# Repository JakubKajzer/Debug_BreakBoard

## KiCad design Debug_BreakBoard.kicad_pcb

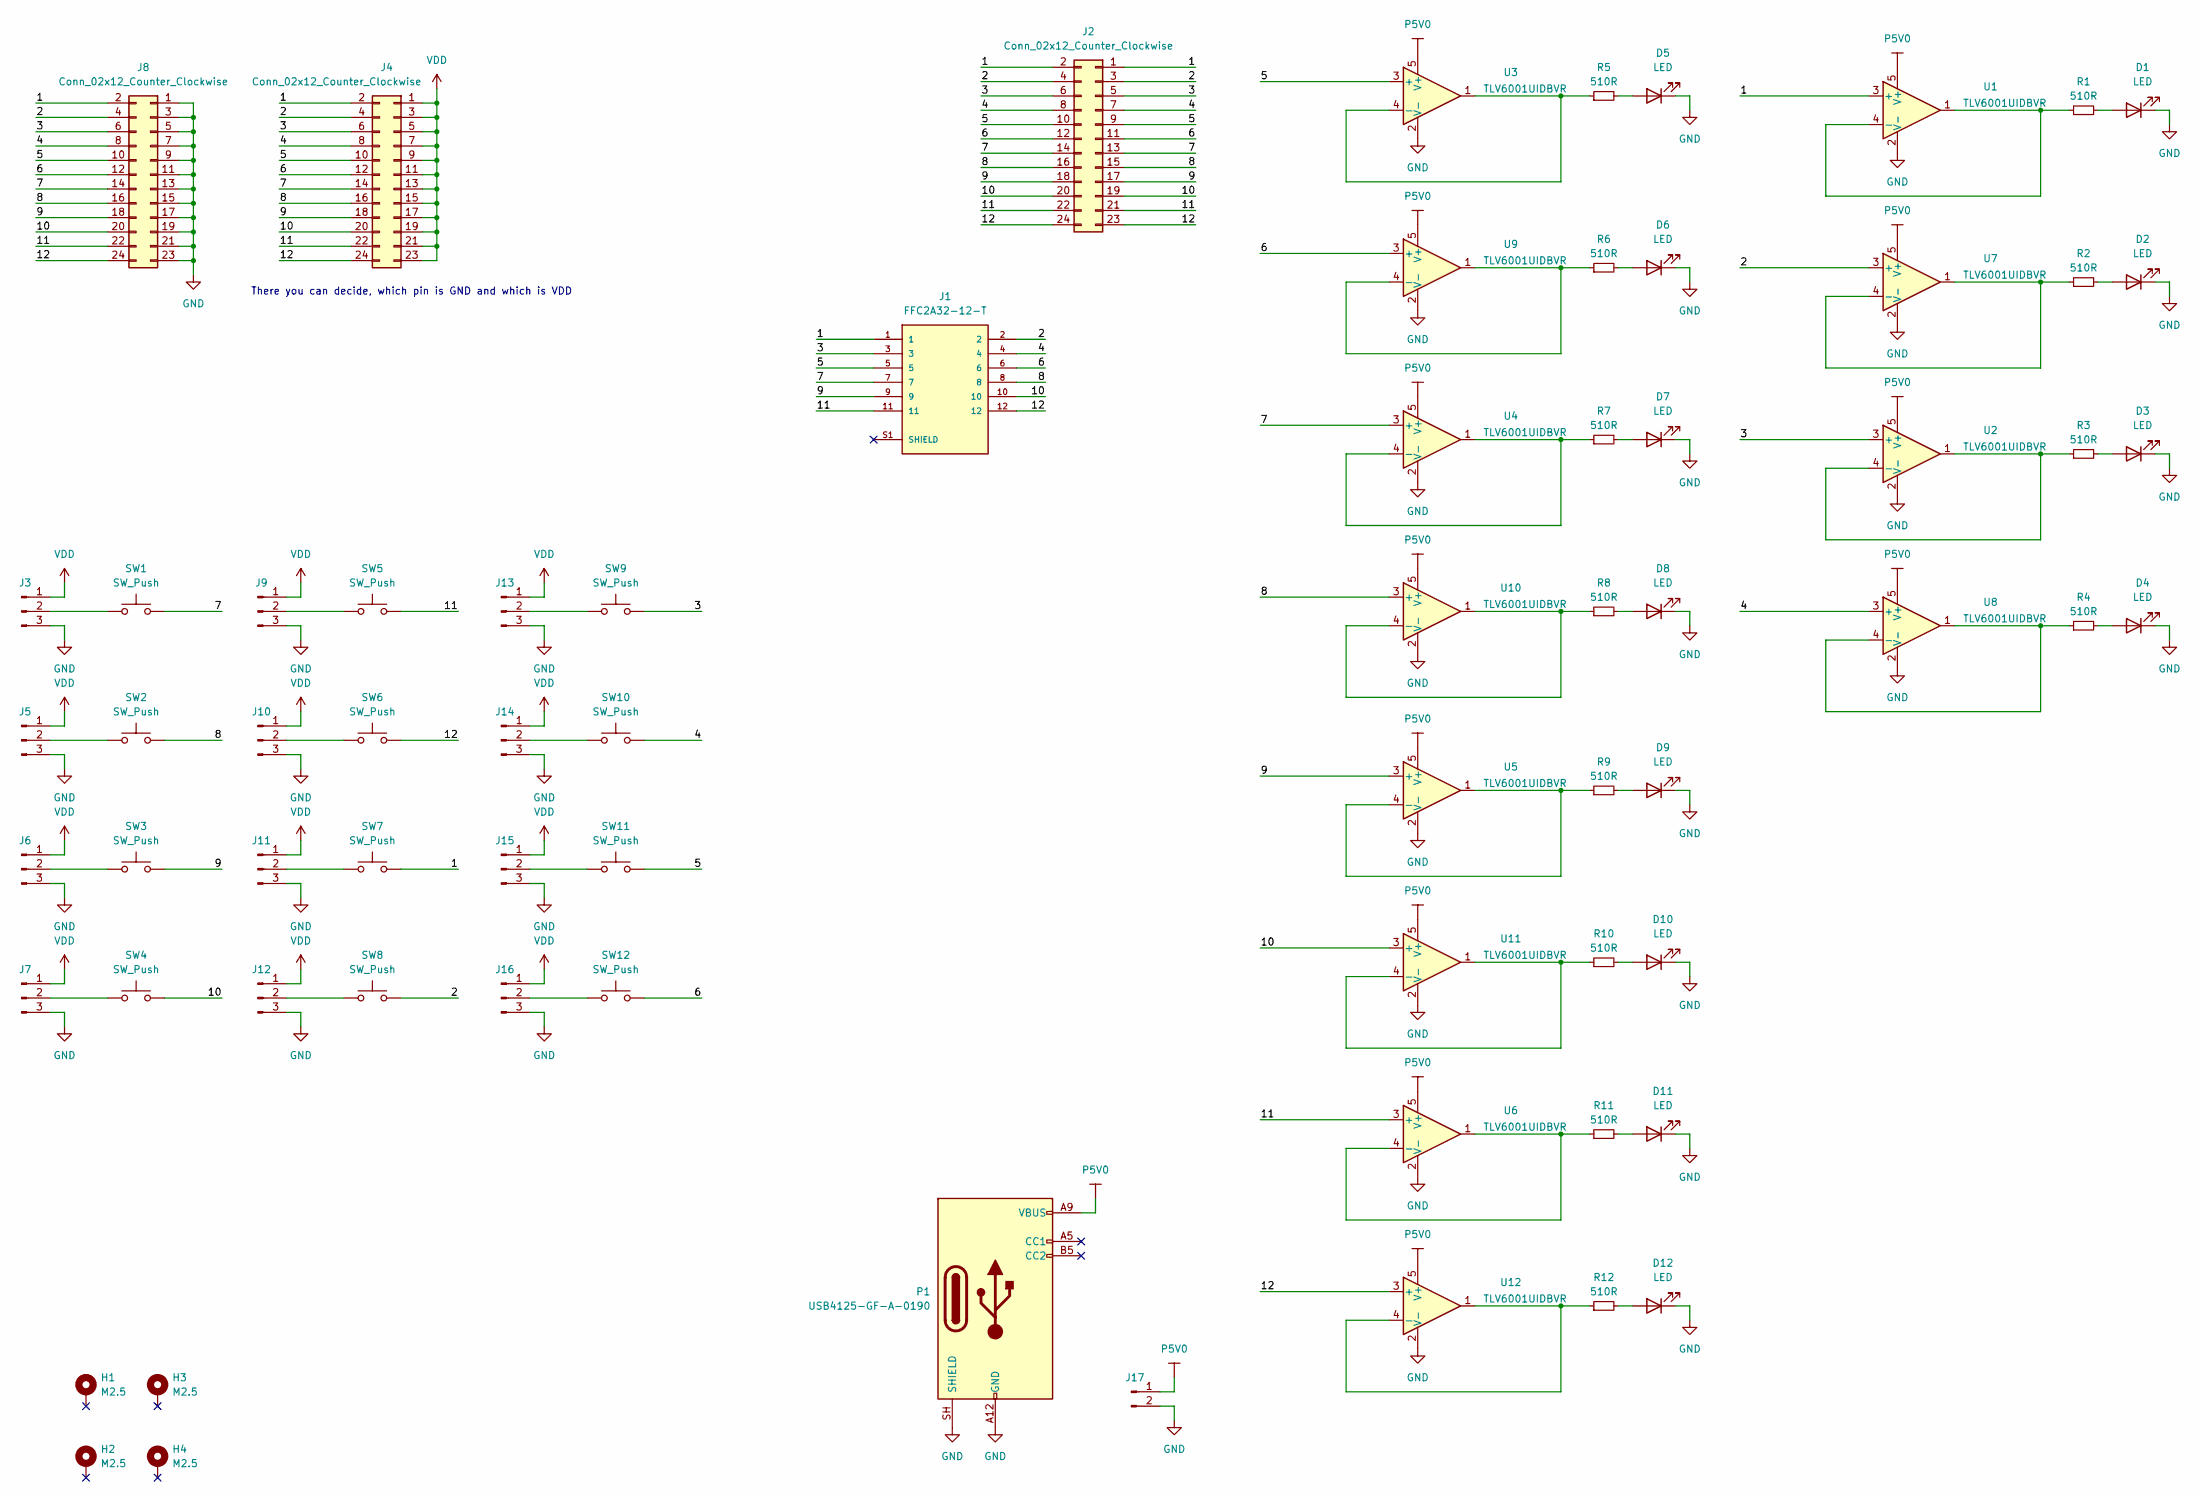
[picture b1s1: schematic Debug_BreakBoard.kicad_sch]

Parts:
D1, D2, D3, D4, D5, D6, D7, D8, D9, D10, D11, D12: LED; LED_0603_1608Metric_Pad1.05x0.95mm_HandSolder; Part Number 150060BS75000
H1, H2, H3, H4: M2.5; MountingHole_2.7mm_M2.5_ISO7380_Pad
J1: FFC2A32-12-T; Part Number FFC2A32-12-T
J2, J4, J8: Conn_02x12_Counter_Clockwise; PinHeader_2x12_P2.54mm_Vertical; Part Number 10129381-924001BLF
J3, J5, J6, J7, J9, J10, J11, J12, J13, J14, J15, J16: Conn_01x03_Pin; PinHeader_1x03_P2.54mm_Vertical; Part Number 68002-403HLF
J17: Conn_01x02_Pin; PinHeader_1x02_P2.54mm_Vertical
P1: USB4125-GF-A-0190; Part Number USB4125-GF-A-0190
R1, R2, R3, R4, R5, R6, R7, R8, R9, R10, R11, R12: 510R; R_0603_1608Metric_Pad0.98x0.95mm_HandSolder; Part Number RMC1/16-511JTP
SW1, SW2, SW3, SW4, SW5, SW6, SW7, SW8, SW9, SW10, SW11, SW12: SW_Push; SW_PUSH_6mm_H5mm; Part Number TS02-66-70-BK-100-SCR-D
U1, U2, U3, U4, U5, U6, U7, U8, U9, U10, U11, U12: TLV6001UIDBVR; SOT-23-5; Part Number TLV6001UIDBVR

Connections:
/1: J1.1, J2.1, J2.2, J4.2, J8.2, SW7.2, U1.3 (+)
/2: J1.2, J2.3, J2.4, J4.4, J8.4, SW8.2, U7.3 (+)
/3: J1.3, J2.5, J2.6, J4.6, J8.6, SW9.2, U2.3 (+)
/4: J1.4, J2.7, J2.8, J4.8, J8.8, SW10.2, U8.3 (+)
/5: J1.5, J2.9, J2.10, J4.10, J8.10, SW11.2, U3.3 (+)
/6: J1.6, J2.11, J2.12, J4.12, J8.12, SW12.2, U9.3 (+)
/7: J1.7, J2.13, J2.14, J4.14, J8.14, SW1.2, U4.3 (+)
/8: J1.8, J2.15, J2.16, J4.16, J8.16, SW2.2, U10.3 (+)
/9: J1.9, J2.17, J2.18, J4.18, J8.18, SW3.2, U5.3 (+)
/10: J1.10, J2.19, J2.20, J4.20, J8.20, SW4.2, U11.3 (+)
/11: J1.11, J2.21, J2.22, J4.22, J8.22, SW5.2, U6.3 (+)
/12: J1.12, J2.23, J2.24, J4.24, J8.24, SW6.2, U12.3 (+)
GND: D1.1 (K), D2.1 (K), D3.1 (K), D4.1 (K), D5.1 (K), D6.1 (K), D7.1 (K), D8.1 (K), D9.1 (K), D10.1 (K), D11.1 (K), D12.1 (K), J3.3, J5.3, J6.3, J7.3, J8.1, J8.3, J8.5, J8.7, J8.9, J8.11, J8.13, J8.15, J8.17, J8.19, J8.21, J8.23, J9.3, J10.3, J11.3, J12.3, J13.3, J14.3, J15.3, J16.3, J17.2, P1.A12 (GND), P1.B12 (GND), P1.SH (SHIELD), U1.2 (V-), U2.2 (V-), U3.2 (V-), U4.2 (V-), U5.2 (V-), U6.2 (V-), U7.2 (V-), U8.2 (V-), U9.2 (V-), U10.2 (V-), U11.2 (V-), U12.2 (V-)
unnamed: D1.2 (A), R1.2
unnamed: D2.2 (A), R2.2
unnamed: D3.2 (A), R3.2
unnamed: D4.2 (A), R4.2
unnamed: D5.2 (A), R5.2
unnamed: D6.2 (A), R6.2
unnamed: D7.2 (A), R7.2
unnamed: D8.2 (A), R8.2
unnamed: D9.2 (A), R9.2
unnamed: D10.2 (A), R10.2
unnamed: D11.2 (A), R11.2
unnamed: D12.2 (A), R12.2
unnamed: J3.2, SW1.1
unnamed: J5.2, SW2.1
unnamed: J6.2, SW3.1
unnamed: J7.2, SW4.1
unnamed: J9.2, SW5.1
unnamed: J10.2, SW6.1
unnamed: J11.2, SW7.1
unnamed: J12.2, SW8.1
unnamed: J13.2, SW9.1
unnamed: J14.2, SW10.1
unnamed: J15.2, SW11.1
unnamed: J16.2, SW12.1
unnamed: R1.1, U1.1, U1.4 (-)
unnamed: R3.1, U2.1, U2.4 (-)
unnamed: R5.1, U3.1, U3.4 (-)
unnamed: R7.1, U4.1, U4.4 (-)
unnamed: R9.1, U5.1, U5.4 (-)
unnamed: R11.1, U6.1, U6.4 (-)
unnamed: R2.1, U7.1, U7.4 (-)
unnamed: R4.1, U8.1, U8.4 (-)
unnamed: R6.1, U9.1, U9.4 (-)
unnamed: R8.1, U10.1, U10.4 (-)
unnamed: R10.1, U11.1, U11.4 (-)
unnamed: R12.1, U12.1, U12.4 (-)
P5V0: J17.1, P1.A9 (VBUS), P1.B9 (VBUS), U1.5 (V+), U2.5 (V+), U3.5 (V+), U4.5 (V+), U5.5 (V+), U6.5 (V+), U7.5 (V+), U8.5 (V+), U9.5 (V+), U10.5 (V+), U11.5 (V+), U12.5 (V+)
VDD: J3.1, J4.1, J4.3, J4.5, J4.7, J4.9, J4.11, J4.13, J4.15, J4.17, J4.19, J4.21, J4.23, J5.1, J6.1, J7.1, J9.1, J10.1, J11.1, J12.1, J13.1, J14.1, J15.1, J16.1

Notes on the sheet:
There you can decide, which pin is GND and which is VDD

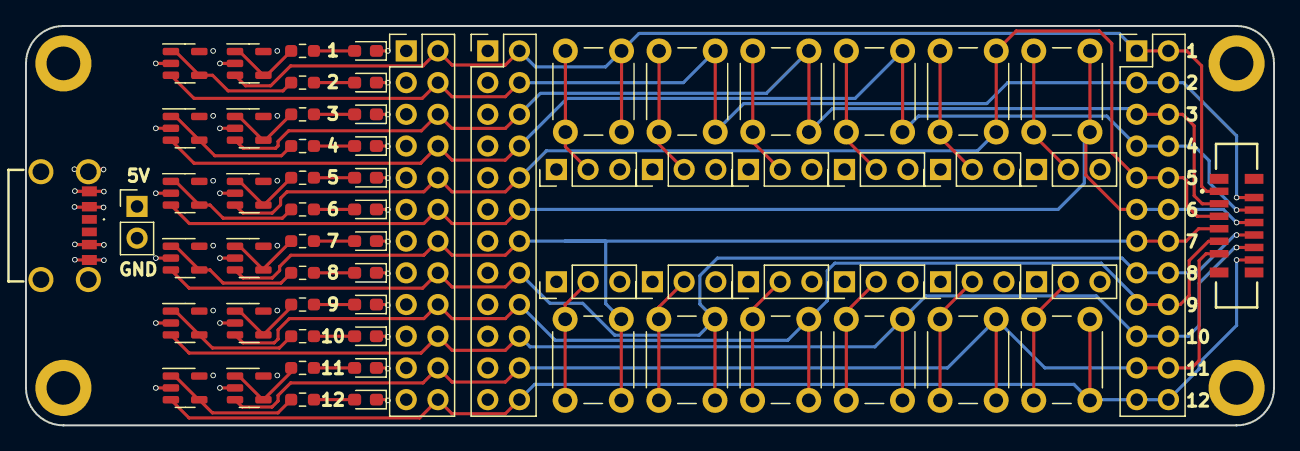
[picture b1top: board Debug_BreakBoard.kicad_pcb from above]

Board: 4 copper layers, 100.0 x 32.0 mm, 70 parts (0 on the bottom side), 51 nets.

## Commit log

2023-07-18 init
2023-07-18 done
